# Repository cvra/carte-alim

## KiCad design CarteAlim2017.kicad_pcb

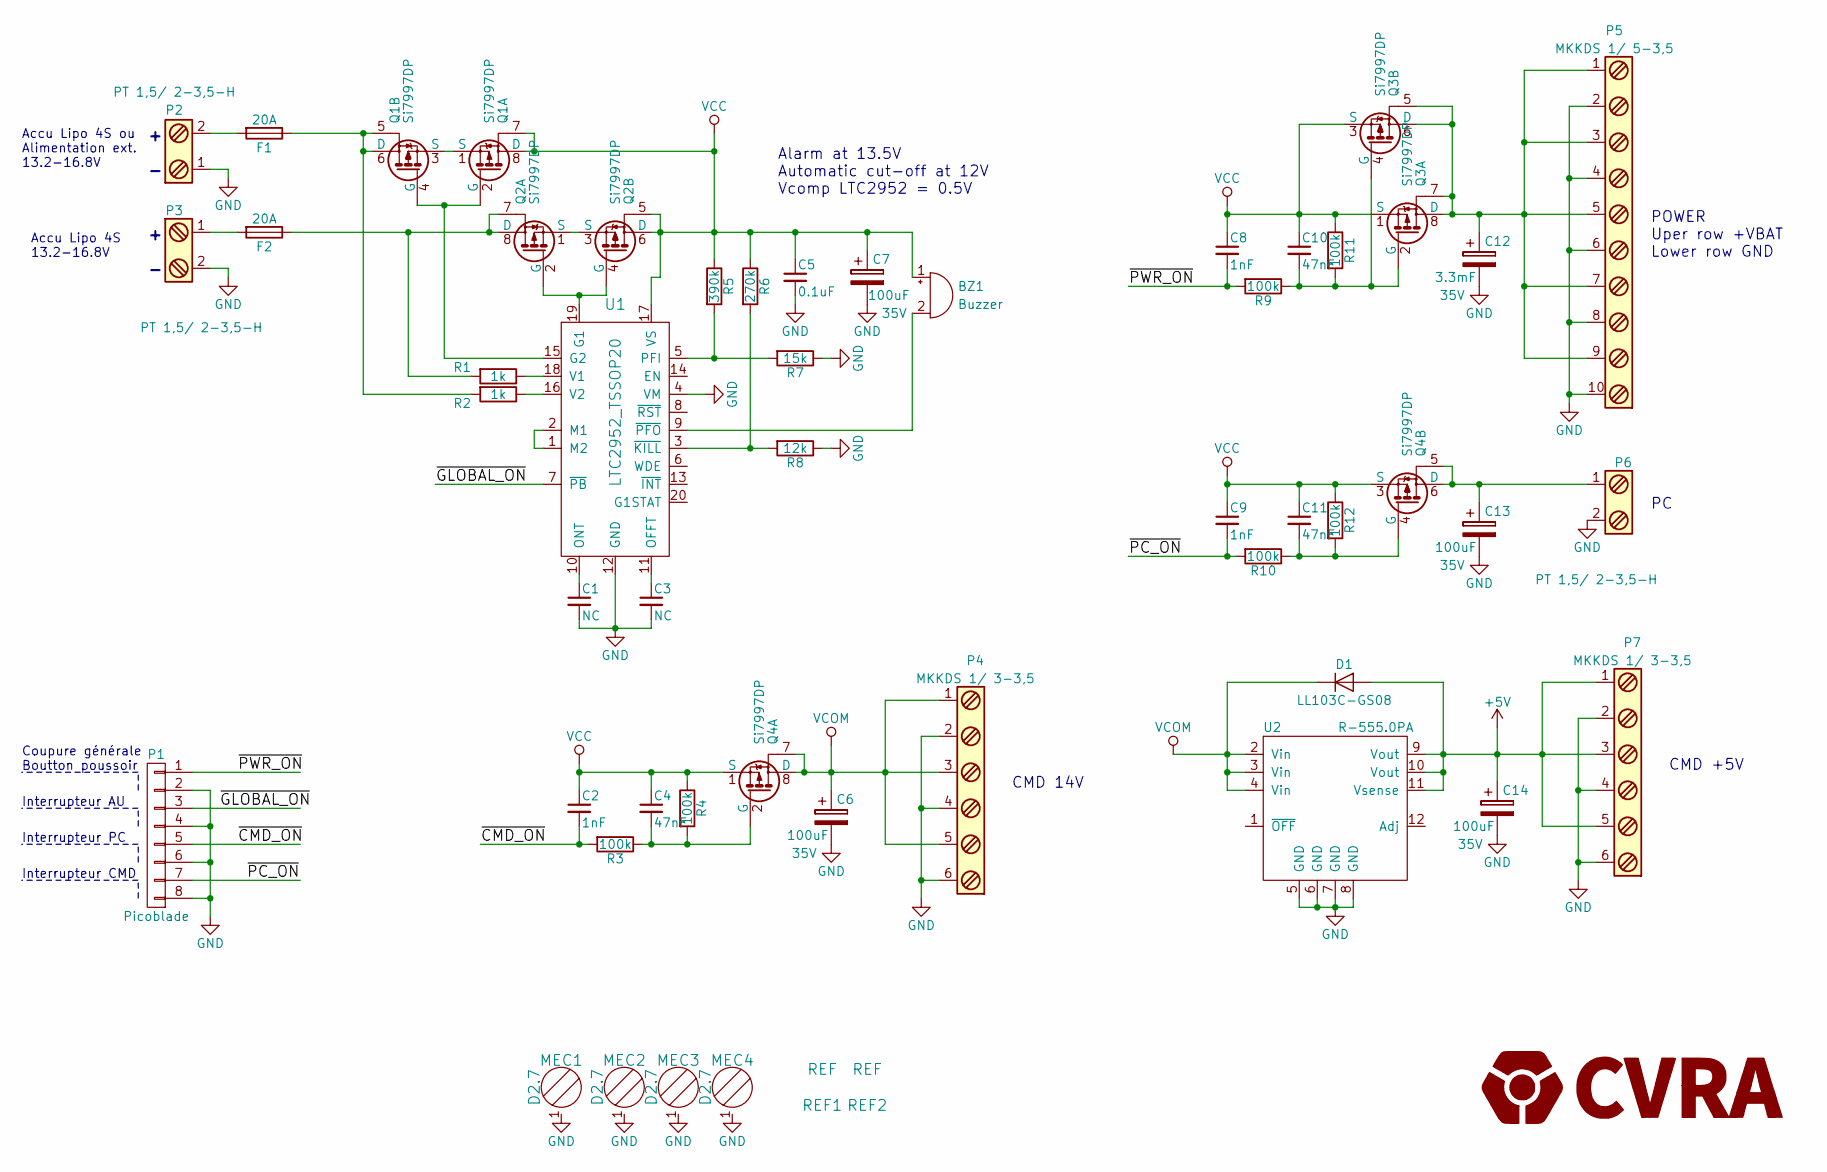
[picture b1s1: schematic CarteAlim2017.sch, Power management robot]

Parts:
BZ1: Buzzer; _Buzzer_PUIAudio_AI-1433-TWT-R; Digikey 668-1341-ND
C1, C3: NC; _0603
C2, C8, C9: 1nF; _0603
C4, C10, C11: 47nF; _0603
C5: 0.1uF; _0603
C6, C7, C13, C14: 100uF; CP_Radial_D8.0mm_P3.50mm; Digikey P12392-ND
C12: 3.3mF; CP_Radial_L31.50D16.00P7.50_H; Digikey 565-3927-ND
D1: LL103C-GS08; D_MiniMELF_Standard
F1, F2: 20A; FuseHolder-Keystone-3557-2
MEC1, MEC2, MEC3, MEC4: D2.7; MountingHole_2.7mm_M2.5_Pad_Via
P1: Picoblade; Molex-PicoBlade-8
P2, P3, P6: PT 1,5/ 2-3,5-H; Bornier_2p_3.5H
P4, P7: MKKDS 1/ 3-3,5; _Pheonix_MKKDS-1-3-3.5mm
P5: MKKDS 1/ 5-3,5; _Pheonix_MKKDS-1-5-3.5mm
Q1, Q2, Q3, Q4: Si7997DP; PowerPak-SO8_5.15x6.15mm_Pitch1.27mm
R1, R2: 1k; _0603
R3, R4, R9, R10, R11, R12: 100k; _0603
R5: 390k; _0603
R6: 270k; _0603
R7: 15k; _0603
R8: 12k; _0603
REF1, REF2: REF; Fiducial_1mm_Dia_2.54mm_Outer_CopperBottom
U1: LTC2952_TSSOP20; TSSOP-20_4.4x6.5mm_Pitch0.65mm
U2: R-555.0PA; DCDC-Conv_Recom_R-5xxxPA; Digikey 945-2315-5-ND

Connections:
+5V: C14.1, D1.2 (A), P7.1, P7.3, P7.5, U2.9 (Vout), U2.10 (Vout), U2.11 (Vsense)
/~CMD_ON: C2.2, P1.5, R3.2
/~GLOBAL_ON: P1.3, U1.7 (~PB)
/~PC_ON: C9.2, P1.7, R10.2
/~PWR_ON: C8.2, P1.1, R9.2
GND: C1.2, C3.2, C5.2, C6.2, C7.2, C12.2, C13.2, C14.2, MEC1.1, MEC2.1, MEC3.1, MEC4.1, P1.2, P1.4, P1.6, P1.8, P2.1, P3.2, P4.2, P4.4, P4.6, P5.2, P5.4, P5.6, P5.8, P5.10, P6.2, P7.2, P7.4, P7.6, R7.1, R8.1, U1.4 (VM), U1.12 (GND), U2.5 (GND), U2.6 (GND), U2.7 (GND), U2.8 (GND)
unnamed: BZ1.2 (+), U1.9 (~PFO)
unnamed: C1.1, U1.10 (ONT)
unnamed: C3.1, U1.11 (OFFT)
unnamed: C4.2, Q4.2 (G), R3.1, R4.2
unnamed: C10.2, Q3.2 (G), Q3.4 (G), R9.1, R11.2
unnamed: C11.2, Q4.4 (G), R10.1, R12.2
unnamed: C12.1, P5.1, P5.3, P5.5, P5.7, P5.9, Q3.5, Q3.6 (D), Q3.7, Q3.8 (D)
unnamed: C13.1, P6.1, Q4.5, Q4.6 (D)
unnamed: F1.1, Q1.5, Q1.6 (D), R2.2
unnamed: F1.2, P2.2
unnamed: F2.1, Q2.7, Q2.8 (D), R1.2
unnamed: F2.2, P3.1
unnamed: Q1.1 (S), Q1.3 (S)
unnamed: Q1.2 (G), Q1.4 (G), U1.15 (G2)
unnamed: Q2.1 (S), Q2.3 (S)
unnamed: Q2.2 (G), Q2.4 (G), U1.19 (G1)
unnamed: R1.1, U1.18 (V1)
unnamed: R2.1, U1.16 (V2)
unnamed: R5.2, R7.2, U1.5 (PFI)
unnamed: R6.2, R8.2, U1.3 (~KILL)
unnamed: U1.1 (M2), U1.2 (M1)
VCC: BZ1.1 (-), C2.1, C4.1, C5.1, C7.1, C8.1, C9.1, C10.1, C11.1, Q1.7, Q1.8 (D), Q2.5, Q2.6 (D), Q3.1 (S), Q3.3 (S), Q4.1 (S), Q4.3 (S), R4.1, R5.1, R6.1, R11.1, R12.1, U1.17 (VS)
VCOM: C6.1, D1.1 (K), P4.1, P4.3, P4.5, Q4.7, Q4.8 (D), U2.2 (Vin), U2.3 (Vin), U2.4 (Vin)

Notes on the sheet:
POWER Uper row +VBAT Lower row GND
CMD +5V
CMD 14V
Coupure générale Boutton poussoir
Interrupteur AU
Interrupteur PC
Interrupteur CMD
Accu Lipo 4S 13.2-16.8V
Accu Lipo 4S ou Alimentation ext. 13.2-16.8V
+ -
Alarm at 13.5V Automatic cut-off at 12V Vcomp LTC2952 = 0.5V

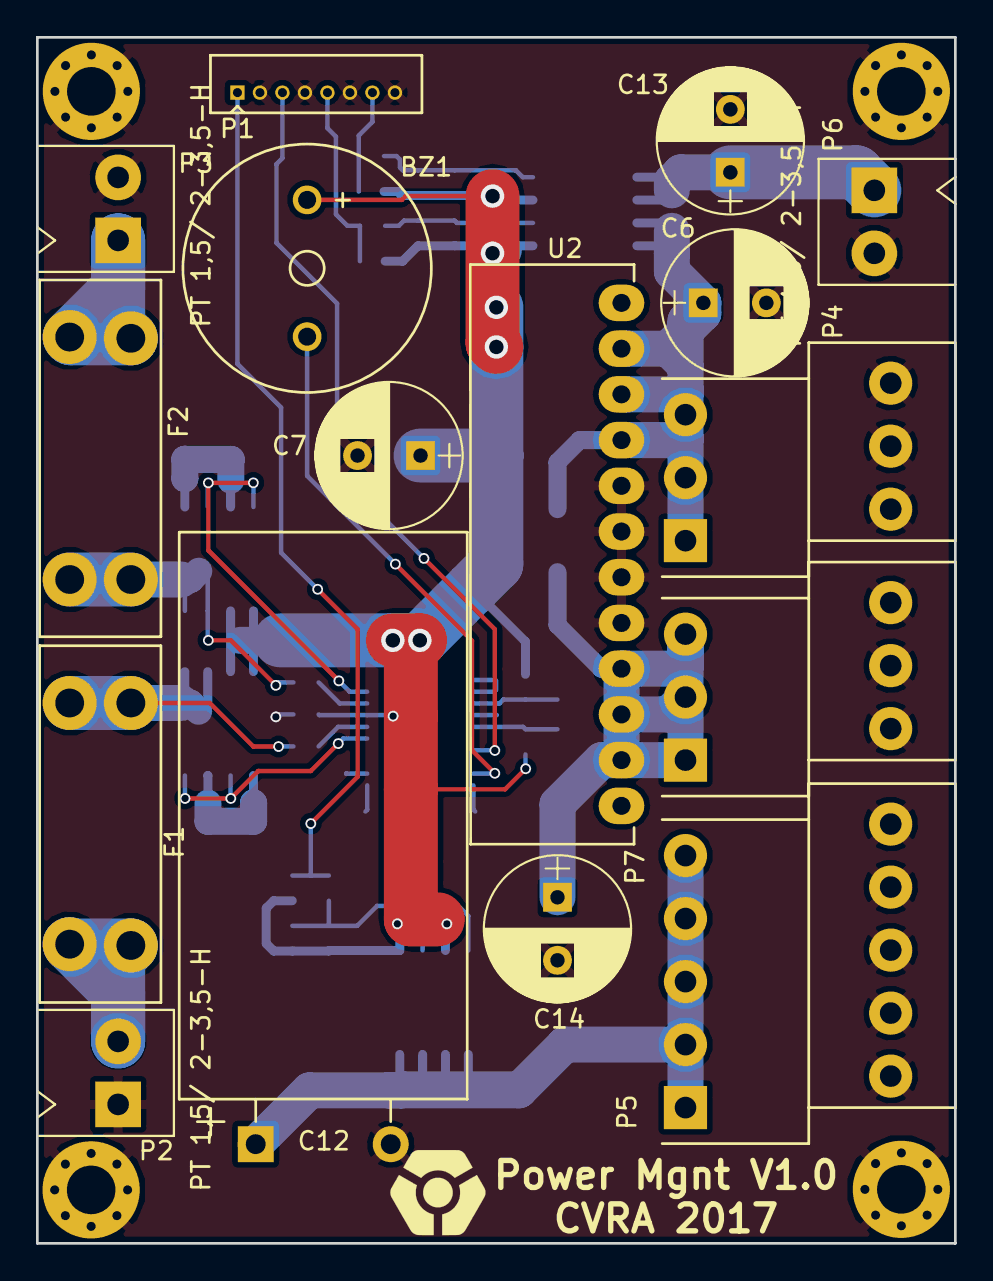
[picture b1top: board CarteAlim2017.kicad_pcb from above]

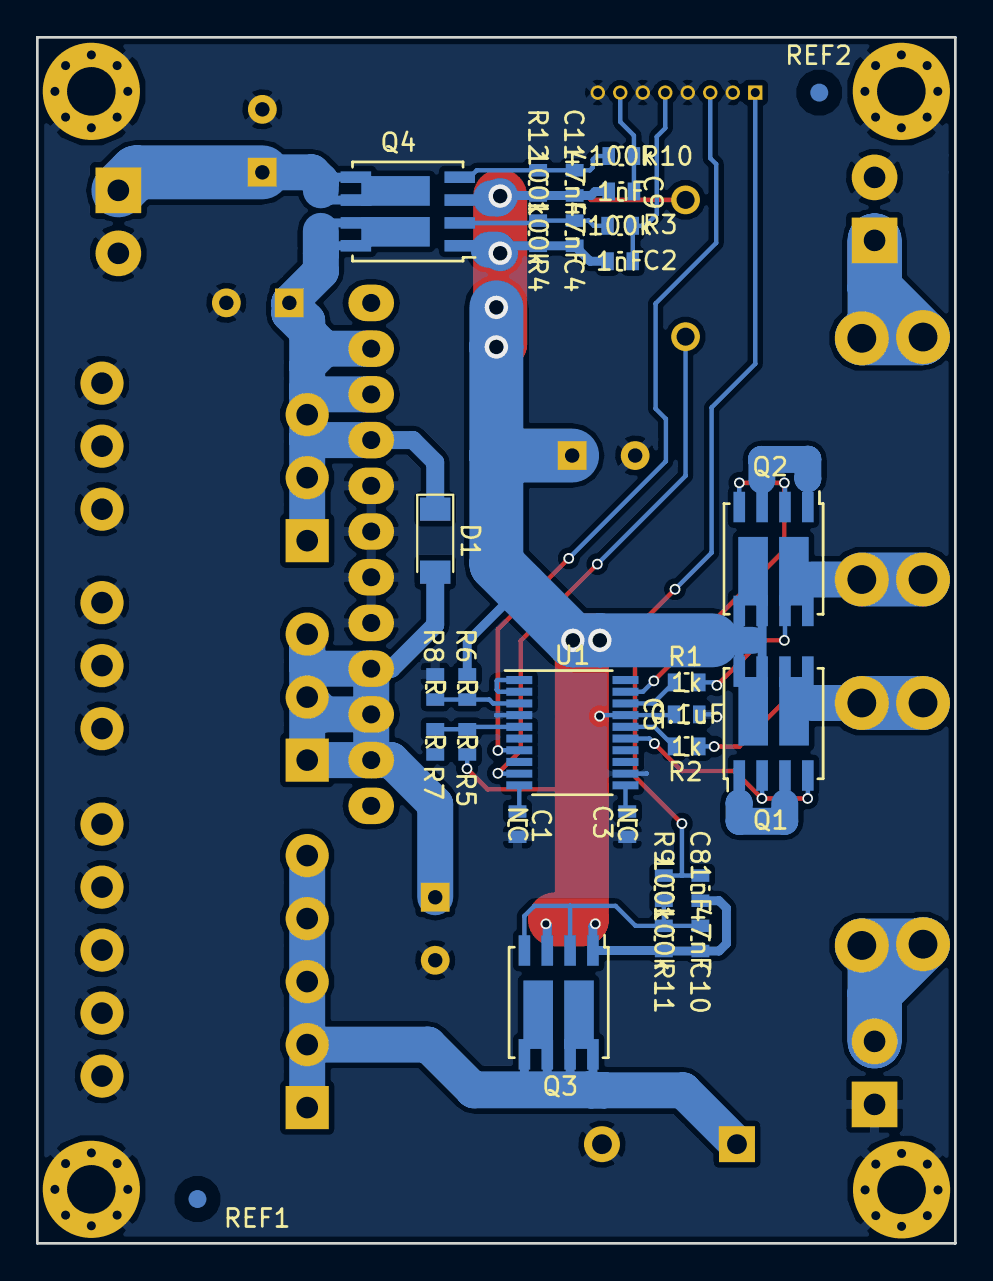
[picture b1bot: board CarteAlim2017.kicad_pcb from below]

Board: 2 copper layers, 51.0 x 67.0 mm, 49 parts (27 on the bottom side), 29 nets.

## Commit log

2020-03-16 Import power supply board project
